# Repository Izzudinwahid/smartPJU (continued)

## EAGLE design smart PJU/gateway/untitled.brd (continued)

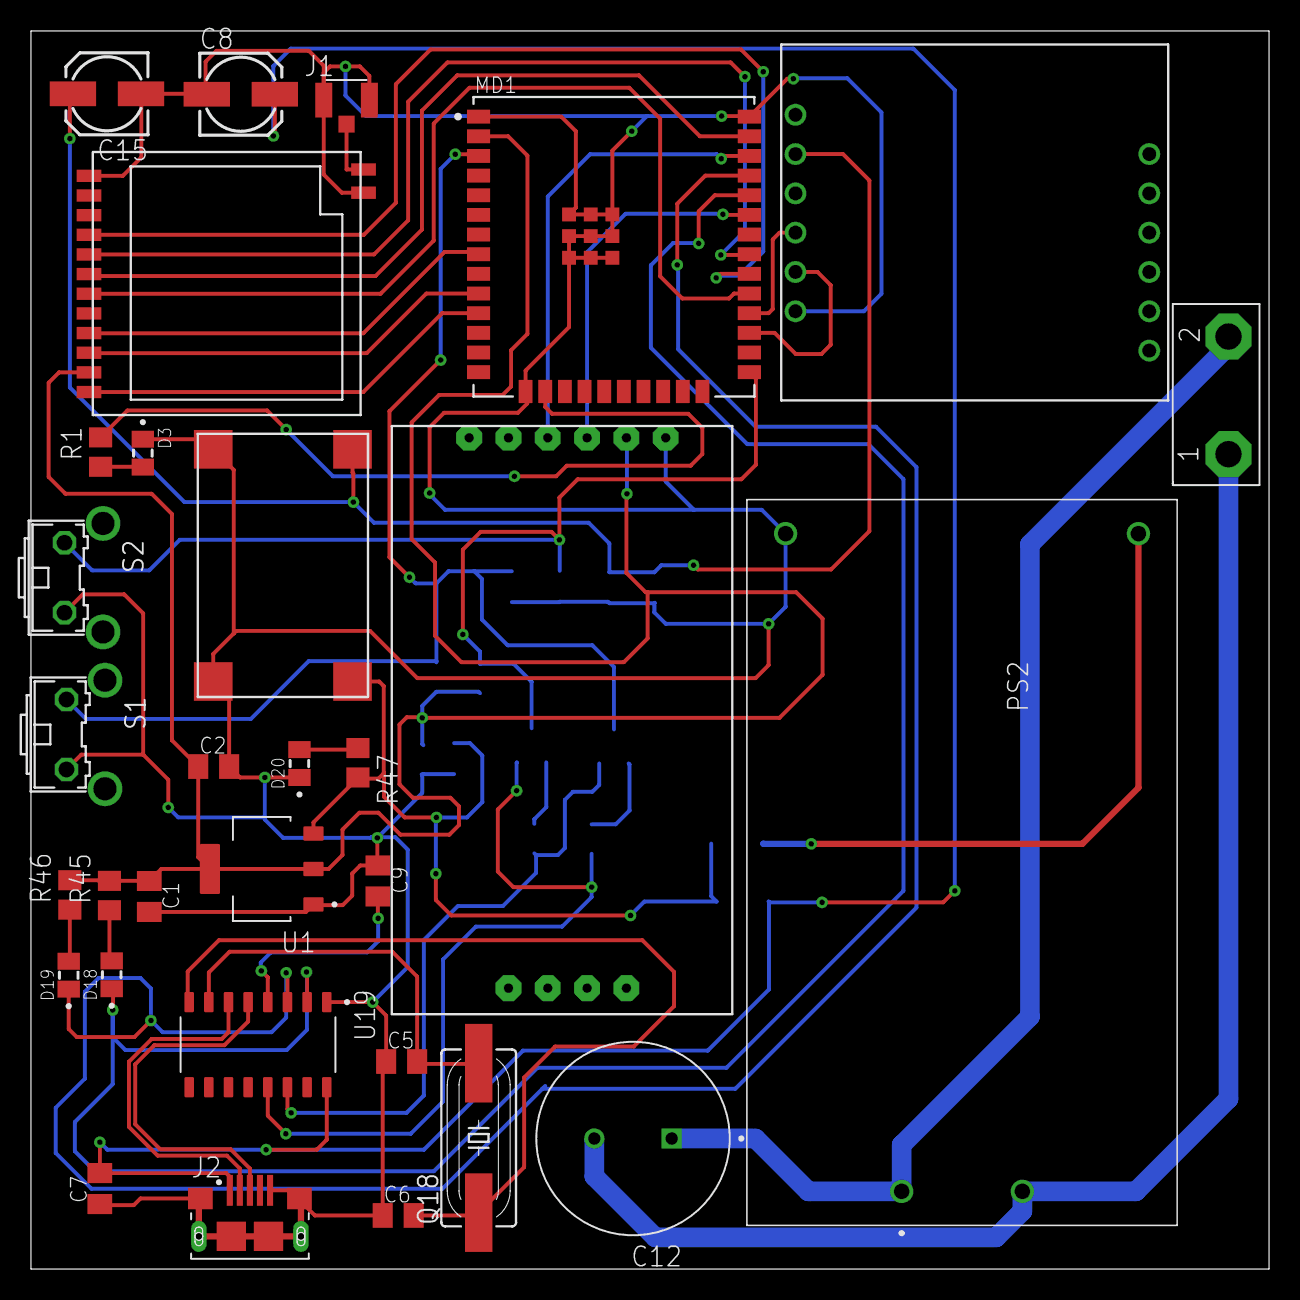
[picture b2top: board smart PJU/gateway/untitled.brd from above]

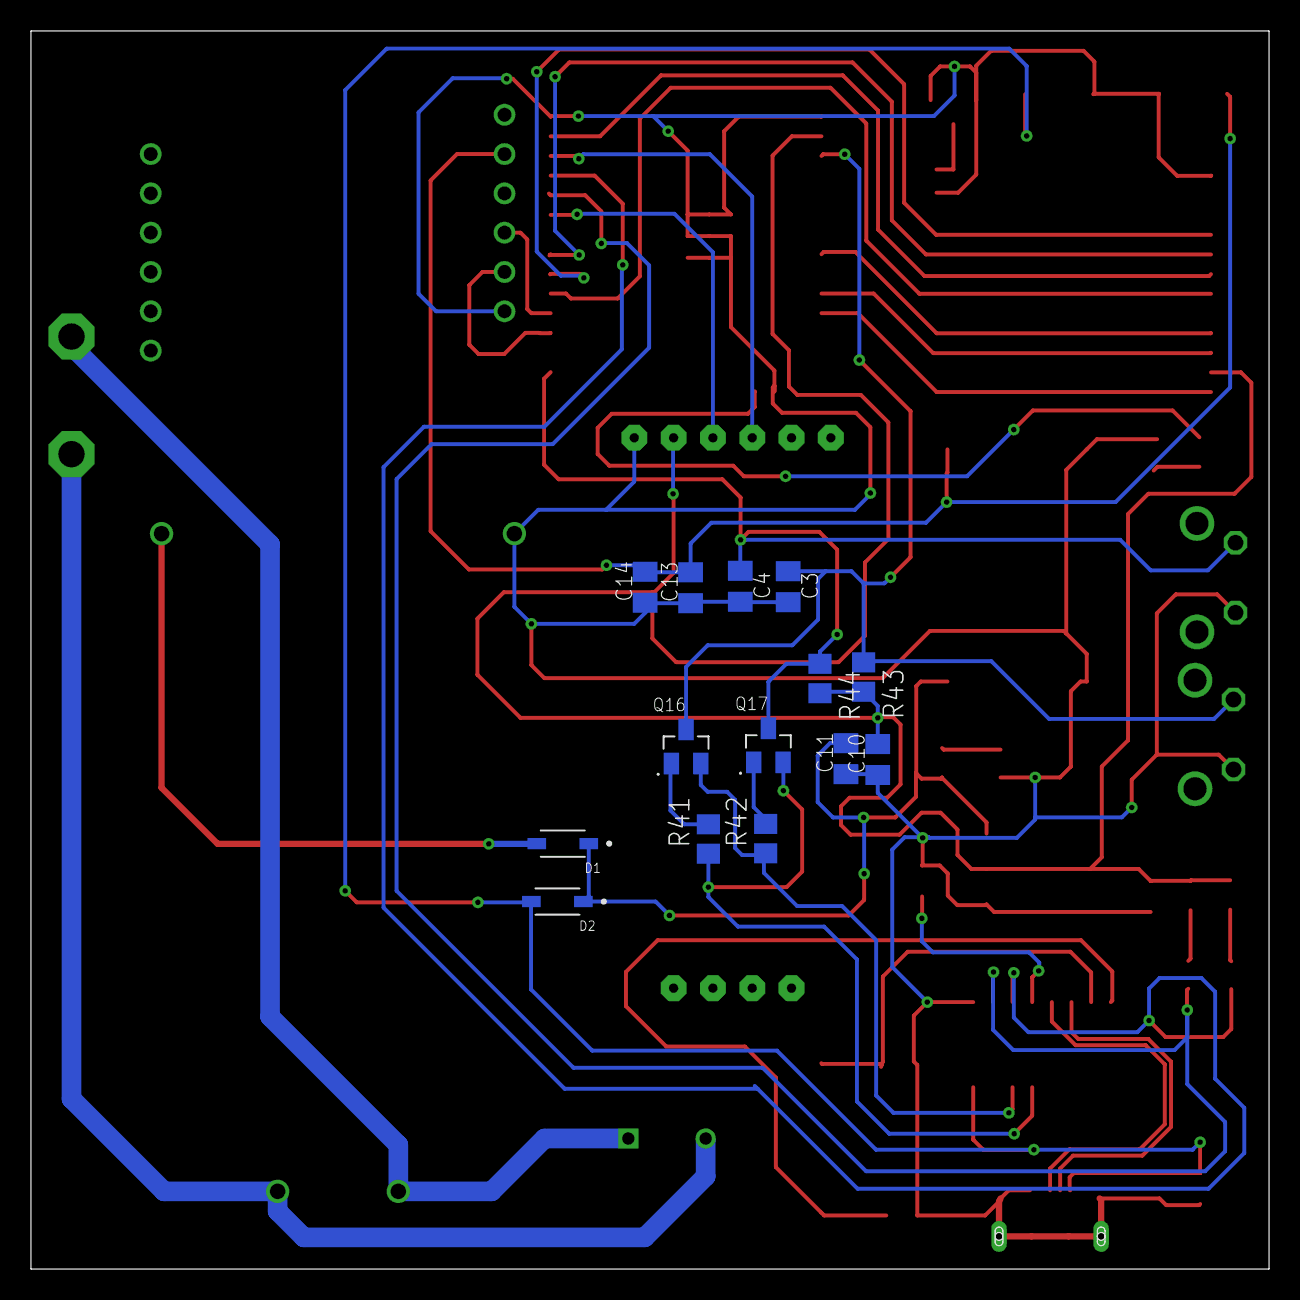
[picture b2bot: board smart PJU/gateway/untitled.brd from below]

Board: 2 copper layers, 80.0 x 80.0 mm, 45 parts (14 on the bottom side), 38 nets.

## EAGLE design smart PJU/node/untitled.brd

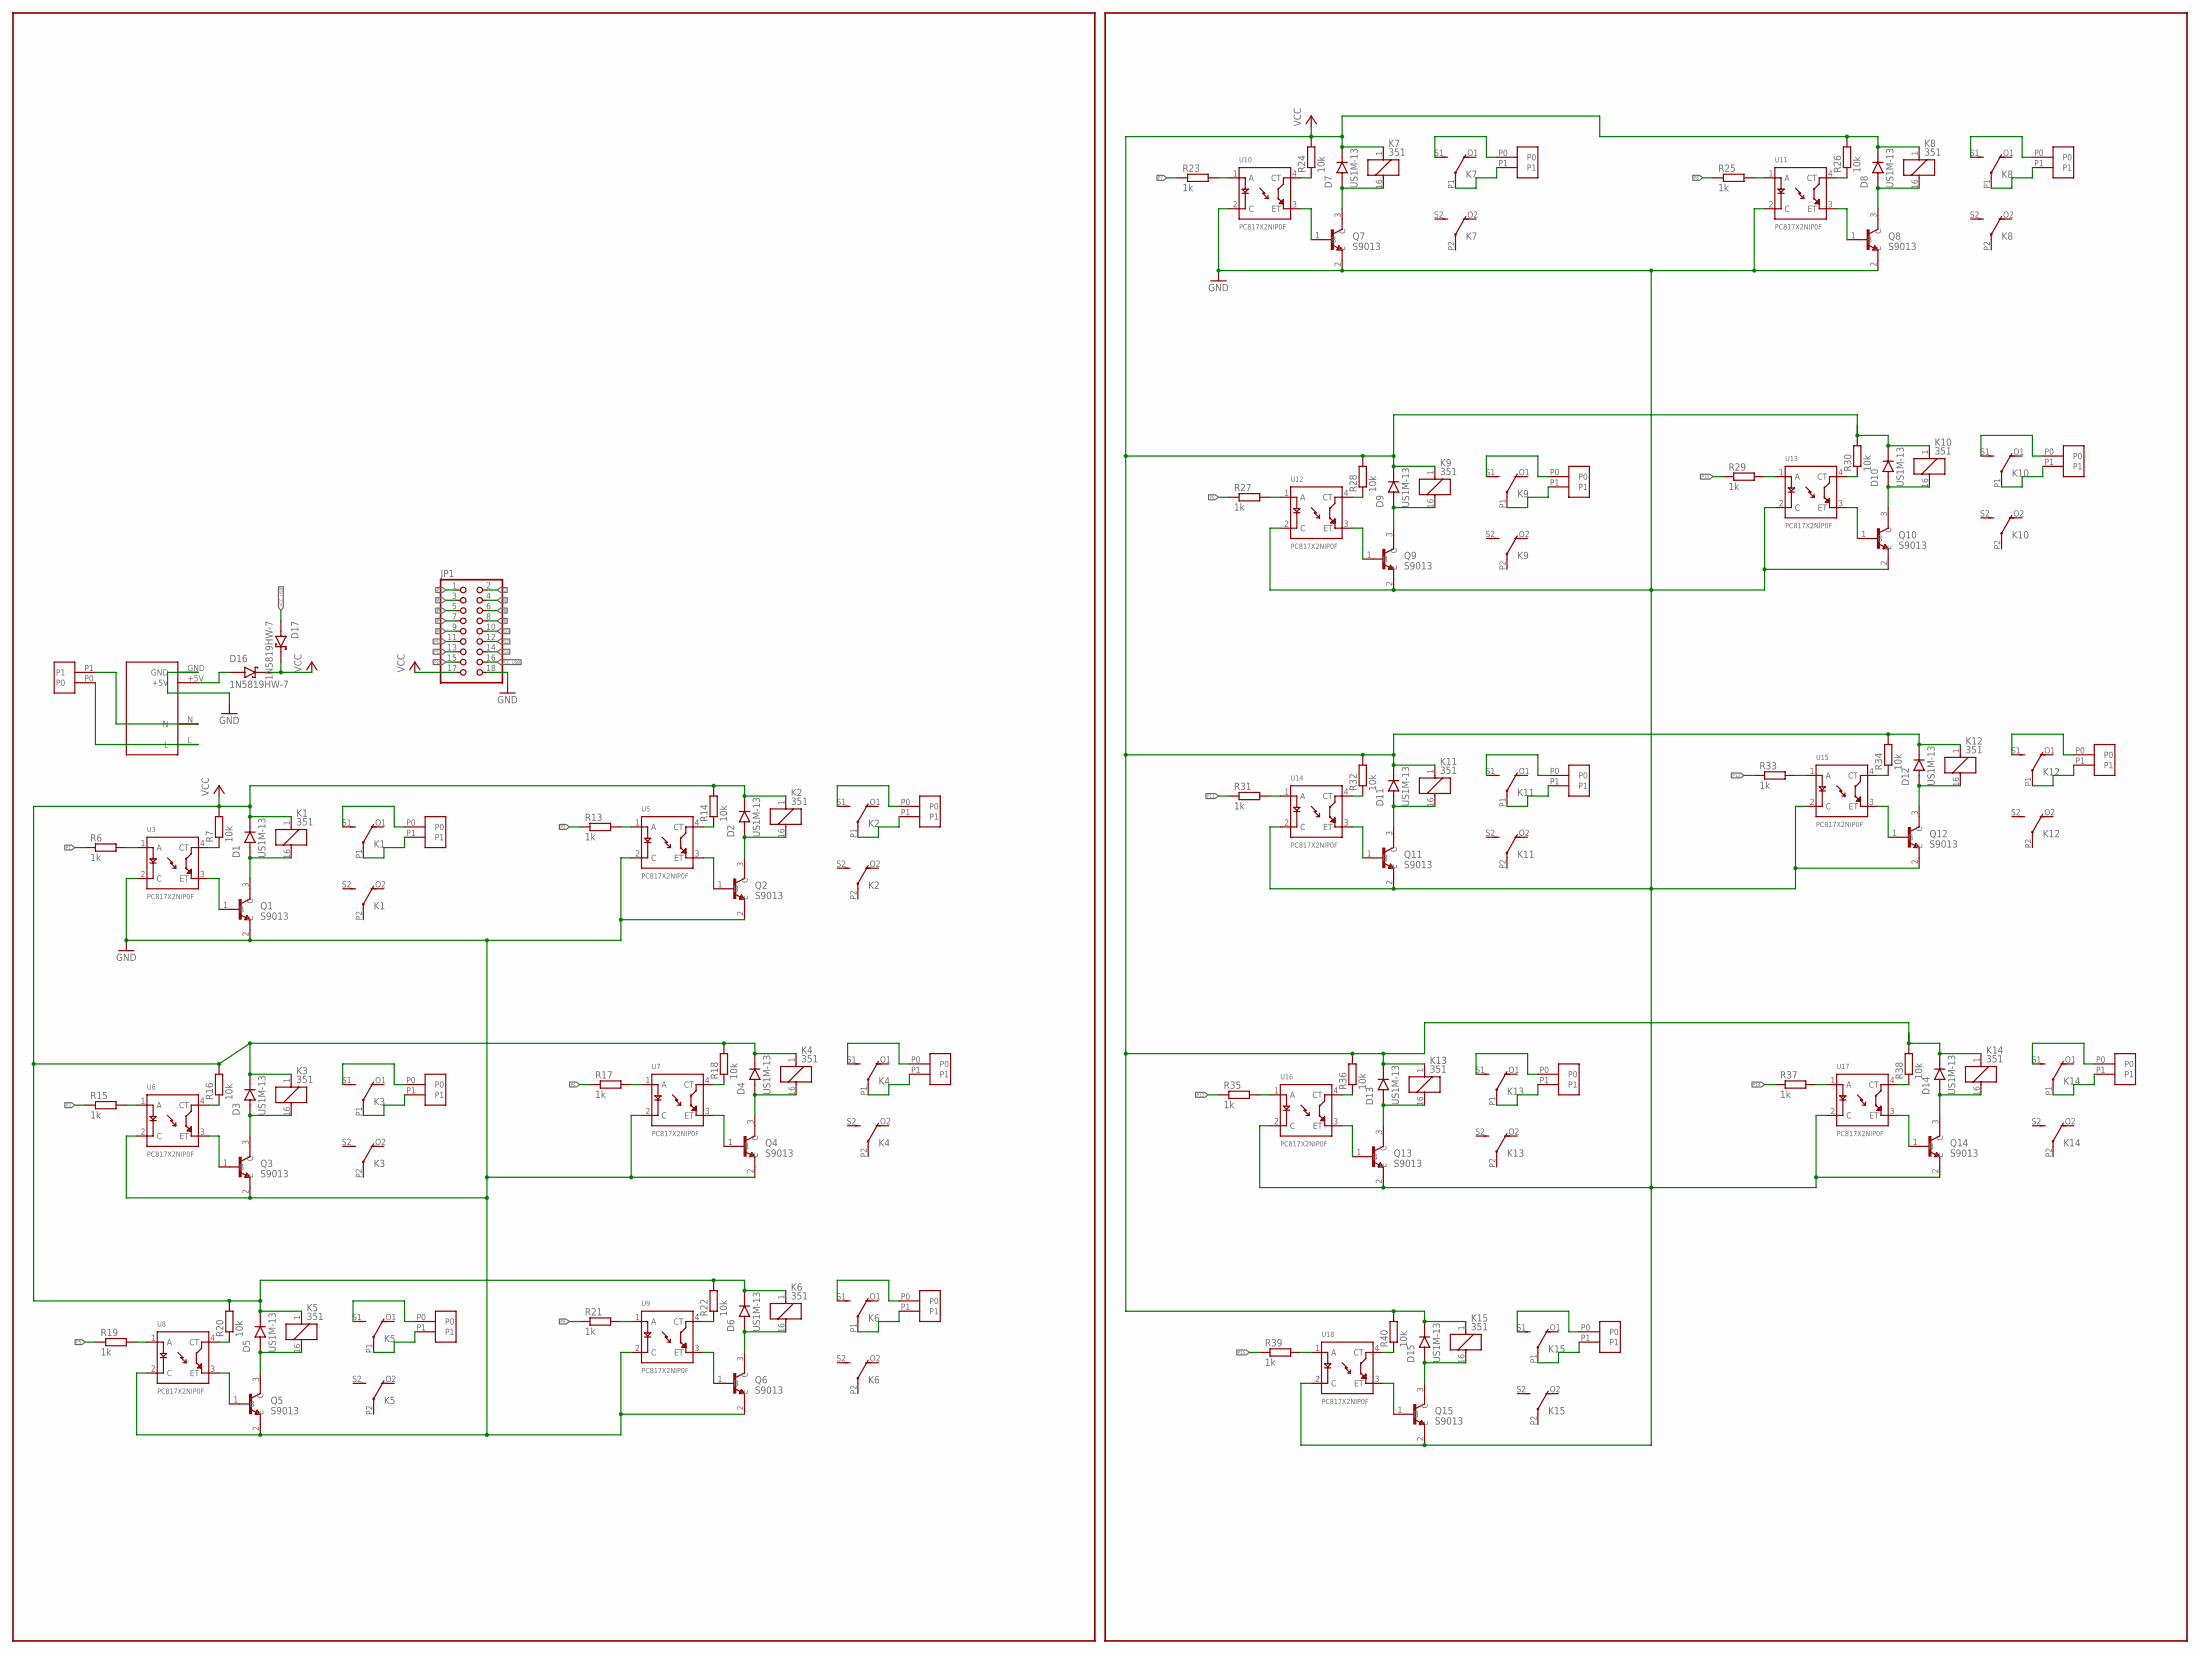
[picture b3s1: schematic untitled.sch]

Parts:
CONN2P-3.5PI1, CONN2P-3.5PI2, CONN2P-3.5PI3, CONN2P-3.5PI4, CONN2P-3.5PI5, CONN2P-3.5PI6, CONN2P-3.5PI7, CONN2P-3.5PI8, CONN2P-3.5PI9, CONN2P-3.5PI10, CONN2P-3.5PI11, CONN2P-3.5PI12, CONN2P-3.5PI13, CONN2P-3.5PI14, CONN2P-3.5PI15, CONN2P-3.5PI16: CONN2P-3.5PI
D1, D2, D3, D4, D5, D6, D7, D8, D9, D10, D11, D12, D13, D14, D15: US1M-13; DIOM5226X240N
D16, D17: 1N5819HW-7; SOD3715X145N
JP1: PINHD-2X9-CBIG; 2X09-CLEANBIG
K1, K2, K3, K4, K5, K6, K7, K8, K9, K10, K11, K12, K13, K14, K15: 351
Q1, Q2, Q3, Q4, Q5, Q6, Q7, Q8, Q9, Q10, Q11, Q12, Q13, Q14, Q15: S9013; SOT95P240X120-3N
R6, R13, R15, R17, R19, R21, R23, R25, R27, R29, R31, R33, R35, R37, R39: 1k; R0805
R7, R14, R16, R18, R20, R22, R24, R26, R28, R30, R32, R34, R36, R38, R40: 10k; R0805
U3, U5, U6, U7, U8, U9, U10, U11, U12, U13, U14, U15, U16, U17, U18: PC817X2NIP0F; SOT254P975X400-4N
WX-DC1: WX-DC12003

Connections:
GND: JP1.18, Q1.2 (E), Q2.2 (E), Q3.2 (E), Q4.2 (E), Q5.2 (E), Q6.2 (E), Q7.2 (E), Q8.2 (E), Q9.2 (E), Q10.2 (E), Q11.2 (E), Q12.2 (E), Q13.2 (E), Q14.2 (E), Q15.2 (E), U3.2 (C), U5.2 (C), U6.2 (C), U7.2 (C), U8.2 (C), U9.2 (C), U10.2 (C), U11.2 (C), U12.2 (C), U13.2 (C), U14.2 (C), U15.2 (C), U16.2 (C), U17.2 (C), U18.2 (C), WX-DC1.GND
unnamed: CONN2P-3.5PI1.P1, WX-DC1.N
unnamed: CONN2P-3.5PI1.P0, WX-DC1.L
unnamed: D16.A, WX-DC1.+5V
unnamed: R6.2, U3.1 (A)
unnamed: R7.1, U3.4 (CT)
unnamed: Q1.1 (B), U3.3 (ET)
unnamed: D1.A, K1.16 (2), Q1.3 (C)
unnamed: CONN2P-3.5PI15.P1, K1.P1
unnamed: CONN2P-3.5PI15.P0, K1.S1 (S)
unnamed: R13.2, U5.1 (A)
unnamed: R14.1, U5.4 (CT)
unnamed: Q2.1 (B), U5.3 (ET)
unnamed: D2.A, K2.16 (2), Q2.3 (C)
unnamed: CONN2P-3.5PI16.P1, K2.P1
unnamed: CONN2P-3.5PI16.P0, K2.S1 (S)
unnamed: R15.2, U6.1 (A)
unnamed: R16.1, U6.4 (CT)
unnamed: Q3.1 (B), U6.3 (ET)
unnamed: D3.A, K3.16 (2), Q3.3 (C)
unnamed: CONN2P-3.5PI2.P1, K3.P1
unnamed: CONN2P-3.5PI2.P0, K3.S1 (S)
unnamed: R17.2, U7.1 (A)
unnamed: R18.1, U7.4 (CT)
unnamed: Q4.1 (B), U7.3 (ET)
unnamed: D4.A, K4.16 (2), Q4.3 (C)
unnamed: CONN2P-3.5PI3.P1, K4.P1
unnamed: CONN2P-3.5PI3.P0, K4.S1 (S)
unnamed: R19.2, U8.1 (A)
unnamed: R20.1, U8.4 (CT)
unnamed: Q5.1 (B), U8.3 (ET)
unnamed: D5.A, K5.16 (2), Q5.3 (C)
unnamed: CONN2P-3.5PI4.P1, K5.P1
unnamed: CONN2P-3.5PI4.P0, K5.S1 (S)
unnamed: R21.2, U9.1 (A)
unnamed: R22.1, U9.4 (CT)
unnamed: Q6.1 (B), U9.3 (ET)
unnamed: D6.A, K6.16 (2), Q6.3 (C)
unnamed: CONN2P-3.5PI5.P1, K6.P1
unnamed: CONN2P-3.5PI5.P0, K6.S1 (S)
unnamed: R23.2, U10.1 (A)
unnamed: R24.1, U10.4 (CT)
unnamed: Q7.1 (B), U10.3 (ET)
unnamed: D7.A, K7.16 (2), Q7.3 (C)
unnamed: CONN2P-3.5PI6.P1, K7.P1
unnamed: CONN2P-3.5PI6.P0, K7.S1 (S)
unnamed: R25.2, U11.1 (A)
unnamed: R26.1, U11.4 (CT)
unnamed: Q8.1 (B), U11.3 (ET)
unnamed: D8.A, K8.16 (2), Q8.3 (C)
unnamed: CONN2P-3.5PI7.P1, K8.P1
unnamed: CONN2P-3.5PI7.P0, K8.S1 (S)
unnamed: R27.2, U12.1 (A)
unnamed: R28.1, U12.4 (CT)
unnamed: Q9.1 (B), U12.3 (ET)
unnamed: D9.A, K9.16 (2), Q9.3 (C)
unnamed: CONN2P-3.5PI8.P1, K9.P1
unnamed: CONN2P-3.5PI8.P0, K9.S1 (S)
unnamed: R29.2, U13.1 (A)
unnamed: R30.1, U13.4 (CT)
unnamed: Q10.1 (B), U13.3 (ET)
unnamed: D10.A, K10.16 (2), Q10.3 (C)
unnamed: CONN2P-3.5PI9.P1, K10.P1
unnamed: CONN2P-3.5PI9.P0, K10.S1 (S)
unnamed: R31.2, U14.1 (A)
unnamed: R32.1, U14.4 (CT)
unnamed: Q11.1 (B), U14.3 (ET)
unnamed: D11.A, K11.16 (2), Q11.3 (C)
unnamed: CONN2P-3.5PI10.P1, K11.P1
unnamed: CONN2P-3.5PI10.P0, K11.S1 (S)
unnamed: R33.2, U15.1 (A)
unnamed: R34.1, U15.4 (CT)
unnamed: Q12.1 (B), U15.3 (ET)
unnamed: D12.A, K12.16 (2), Q12.3 (C)
unnamed: CONN2P-3.5PI11.P1, K12.P1
unnamed: CONN2P-3.5PI11.P0, K12.S1 (S)
unnamed: R35.2, U16.1 (A)
unnamed: R36.1, U16.4 (CT)
unnamed: Q13.1 (B), U16.3 (ET)
unnamed: D13.A, K13.16 (2), Q13.3 (C)
unnamed: CONN2P-3.5PI12.P1, K13.P1
unnamed: CONN2P-3.5PI12.P0, K13.S1 (S)
unnamed: R37.2, U17.1 (A)
unnamed: R38.1, U17.4 (CT)
unnamed: Q14.1 (B), U17.3 (ET)
unnamed: D14.A, K14.16 (2), Q14.3 (C)
unnamed: CONN2P-3.5PI13.P1, K14.P1
unnamed: CONN2P-3.5PI13.P0, K14.S1 (S)
unnamed: R39.2, U18.1 (A)
unnamed: R40.1, U18.4 (CT)
unnamed: Q15.1 (B), U18.3 (ET)
unnamed: D15.A, K15.16 (2), Q15.3 (C)
unnamed: CONN2P-3.5PI14.P1, K15.P1
unnamed: CONN2P-3.5PI14.P0, K15.S1 (S)
P1: JP1.1, R6.1
P2: JP1.2, R13.1
P3: JP1.3, R15.1
P4: JP1.4, R17.1
P5: JP1.5, R19.1
P6: JP1.6, R21.1
P7: JP1.7, R23.1
P8: JP1.8, R25.1
P9: JP1.9, R27.1
P10: JP1.10, R29.1
P11: JP1.11, R31.1
P12: JP1.12, R33.1
P13: JP1.13, R35.1
P14: JP1.14, R37.1
P15: JP1.15, R39.1
VCC: D1.C (K), D2.C (K), D3.C (K), D4.C (K), D5.C (K), D6.C (K), D7.C (K), D8.C (K), D9.C (K), D10.C (K), D11.C (K), D12.C (K), D13.C (K), D14.C (K), D15.C (K), D16.C (K), D17.C (K), JP1.17, K1.1, K2.1, K3.1, K4.1, K5.1, K6.1, K7.1, K8.1, K9.1, K10.1, K11.1, K12.1, K13.1, K14.1, K15.1, R7.2, R14.2, R16.2, R18.2, R20.2, R22.2, R24.2, R26.2, R28.2, R30.2, R32.2, R34.2, R36.2, R38.2, R40.2
VCC_USB: D17.A, JP1.16

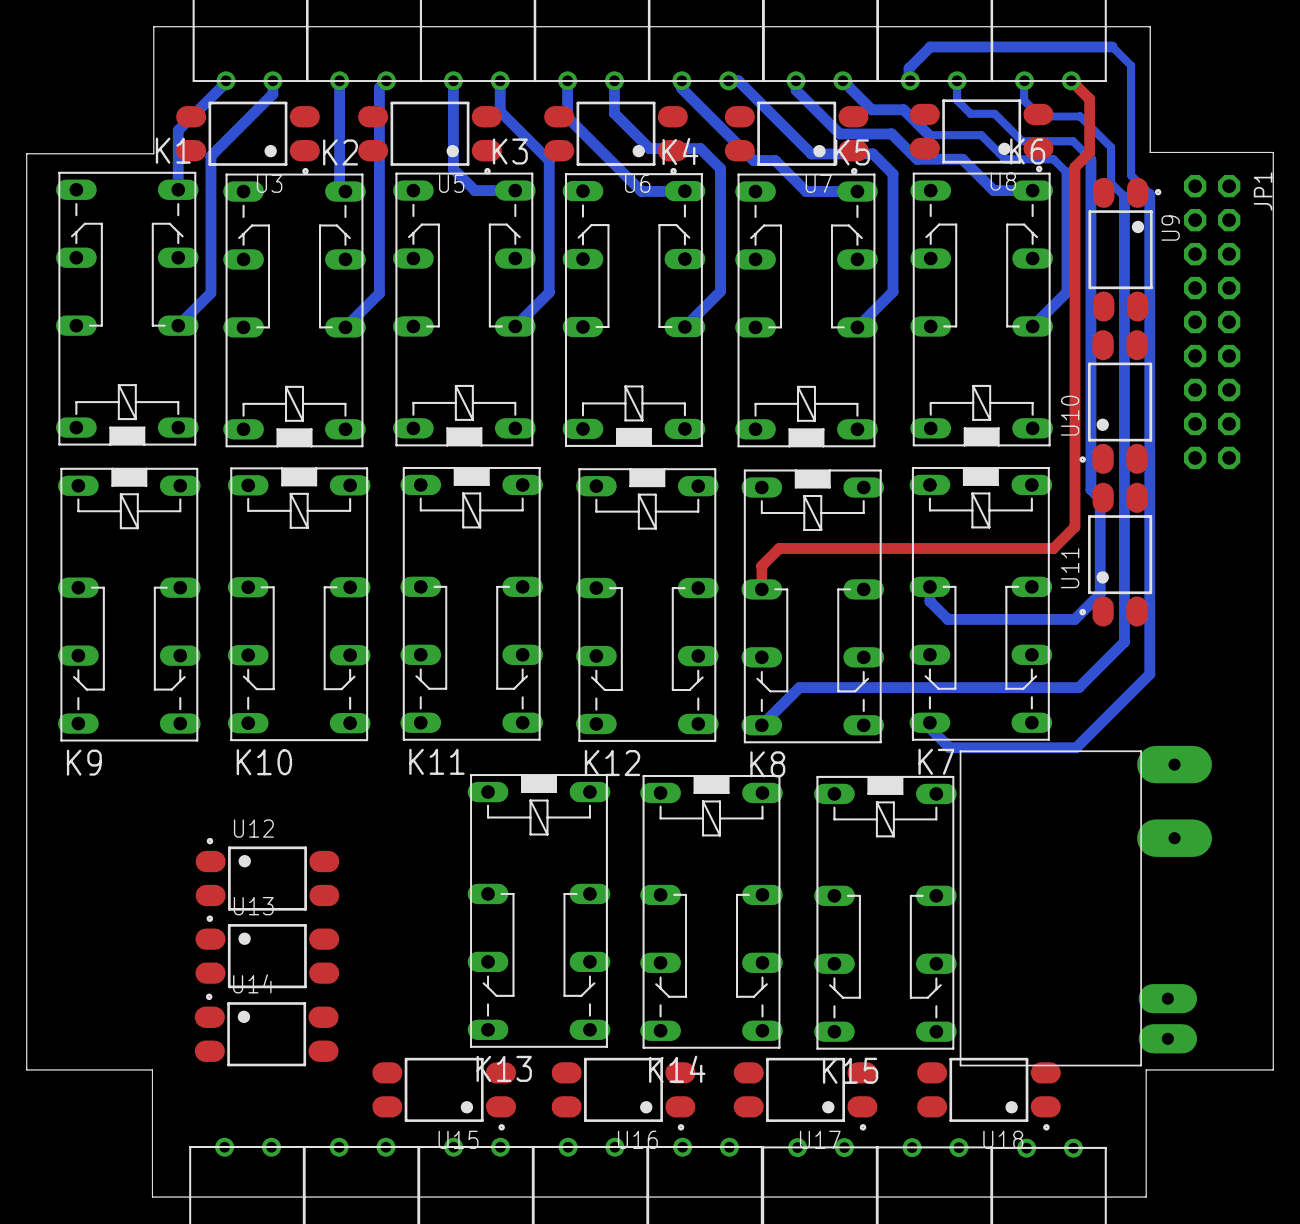
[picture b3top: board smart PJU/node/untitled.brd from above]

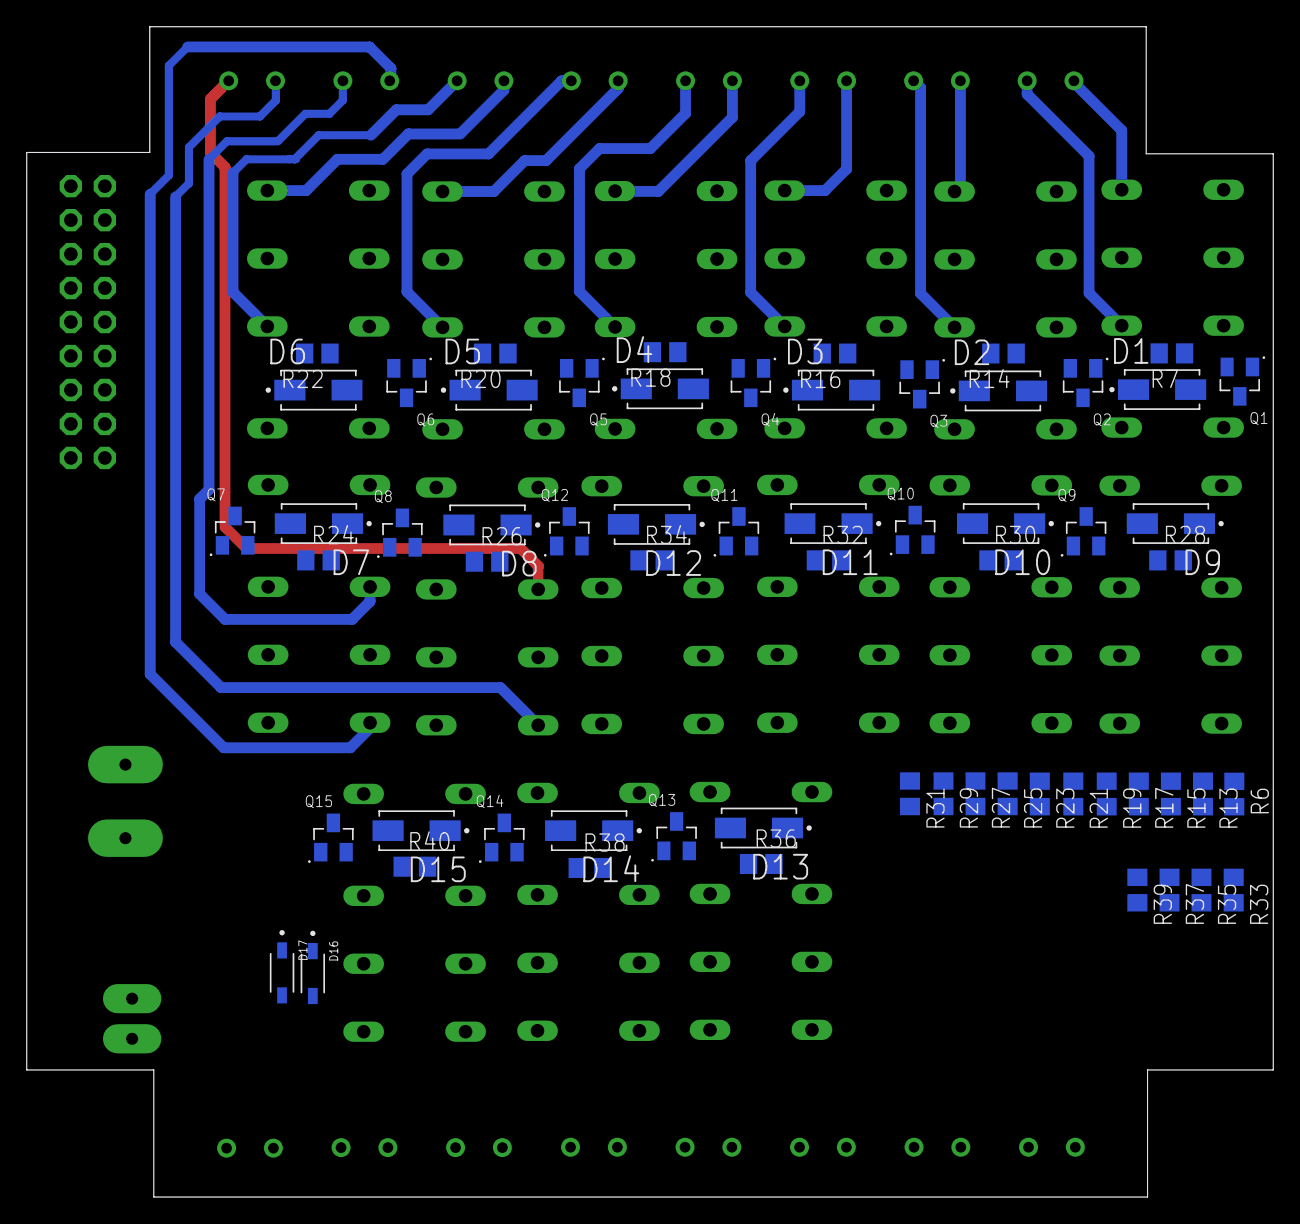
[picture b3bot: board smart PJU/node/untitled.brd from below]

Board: 2 copper layers, 93.2 x 87.5 mm, 110 parts (62 on the bottom side), 111 nets.

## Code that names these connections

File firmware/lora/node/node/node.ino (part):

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int countLamp = 0;

//--------Inisialisasi Sensor PZEM------
#define RX_PZEM 16
#define TX_PZEM 17
PZEM004Tv30 pzem(Serial2, RX_PZEM, TX_PZEM);
String dataSensor[1];

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
      //      EEPROM.write(0, relay);
      statusRelay = relay;
      CONSTANTARELAY = relay;
      HSBtimer = HSBtimerRelay;
      LSBtimer = LSBtimerRelay;
      interval = (HSBtimer * 255 + LSBtimer) * 10;
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
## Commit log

2022-11-28 bismillah sukses
2022-12-07 desain tidak sesuai dengan request client
2022-12-07 rangkaian smartPJU
2022-12-08 membuat PCB gateway
2022-12-11 revisi relay node dan list komponen
2022-12-12 revisi PS hilink 2A
2022-12-18 revisi rangkaian
2022-12-18 .brd
2022-12-18 revisi posisi
2022-12-18 menambahkan fuse
2022-12-28 revisi besar-besaran
2023-01-02 update tanggal 02/01/2023
2023-01-03 update tanggal 03/01/2023
2023-01-05 revisi tanggal 05/01/2023
2023-01-06 revisi tanggal 06/01/2023
2023-01-07 revisi tanggal 07/01/2023
2023-01-07 revisi tanggal 08/01/2023
2023-01-11 revisi tanggal 12/01/2023
2023-01-17 revisi tanggal 17/01/2023
2023-01-24 revisi tanggal 24/01/2023
2023-02-14 revisi tanggal 14/02/2023
2023-02-14 revisi PCB tanggal 14/02/2023
2023-02-15 revisi tanggal 16/02/2023
2023-02-16 revisi tanggal 17/02/2023
2023-02-22 penambahan spiffs
2023-02-23 penambahan file extrack SPIFFS
2023-03-02 revisi reset kwh pzem
2023-03-02 penambahan indikator lampu lora
2023-03-14 revisi tanggal 14/03/2023
2023-03-20 revisi PCB jalur, relay, pzem V dan power 1
2023-03-20 revisi PCB
2023-04-10 revisi firmware tentang jumlah lampu
2023-04-11 default perhitungan lampu
